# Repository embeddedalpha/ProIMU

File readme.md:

# ProIMU (Under Development)
### A high precision interial measurement unit with altitute and GPS support.

### ProIMU can be operated with and without battery. A 3000 mAh LiPo battery powers the device and can be recharged via USB.

### Features available: 
<li>Yaw  (degrees / rad)</li>
<li>Pitch  (degrees / rad)</li>
<li>Roll   (degrees / rad)</li>
<li>Quaternions (degrees / rad)</li>
<li>Pressure (Pa / Hg)</li>
<li>Altitude </li>
<li>Temperature (C / F) </li>
<li>Longitutde </li>
<li>Lattitude </li>
<li>Raw Accelerometer, Gyroscope & Magnetometer </li>
<li>Direction (N/W/E/S) </li>
</br>

### Communication Protocols Available:

<li>USB</li>
<li>TCP IP Socket</li>
<li>MQTT</li>
</br>

### Project Folders:

    📁 Documentation
    📁 Firmware
    📁 Hardware
        ↳ 📁 3D Model
        ↳ 📁 assembly_outputs
        ↳ 📁 BOM
        ↳ 📁 fab_outputs
        ↳ 📁 position_file
        ↳ 📁 footprints.pretty
        ↳ 📁 kicad_proj
            ↳ 📁 ProIMU_V1
        ↳ 📁 lib_fp.pretty
    📁 Images
    📄 README.md

</br>

### Pinout of the MCU:

</br>

### Communication Protocols used:

<table>
    <tr>
        <th> Protocol
        <th> Instance
        <th> Device
    <!-- </tr>
        <tr>
        <td> UART
        <td> 1
        <td> Debug/Console
    </tr> -->
    <!-- <tr>
        <td> 
        <td> 2
        <td> RS232
    </tr> -->
    <tr>
        <td> 
        <td> 1
        <td> Air602 WiFi Module
    </tr>
    <tr>
        <td> 
        <td> 2
        <td> GNSS Module
    </tr>
    <tr>
        <td> I2C
        <td> 2
        <td> MPU9250
    </tr>
    <tr>
        <td> 
        <td> 2
        <td> BMP280
    <!-- </tr>
        <tr>
        <td> 
        <td> 3
        <td> Fuel Gauge
    </tr> -->
    </tr>
    <!-- <tr>
        <td> SPI
        <td> 1
        <td> MPU9250
    </tr> -->
    <tr>
        <td> SDIO
        <td> 1
        <td> SD Card Module
    </tr>
    <tr>
        <td> USB 
        <td> 1
        <td> USB Port
    </tr>
</table>
</br>

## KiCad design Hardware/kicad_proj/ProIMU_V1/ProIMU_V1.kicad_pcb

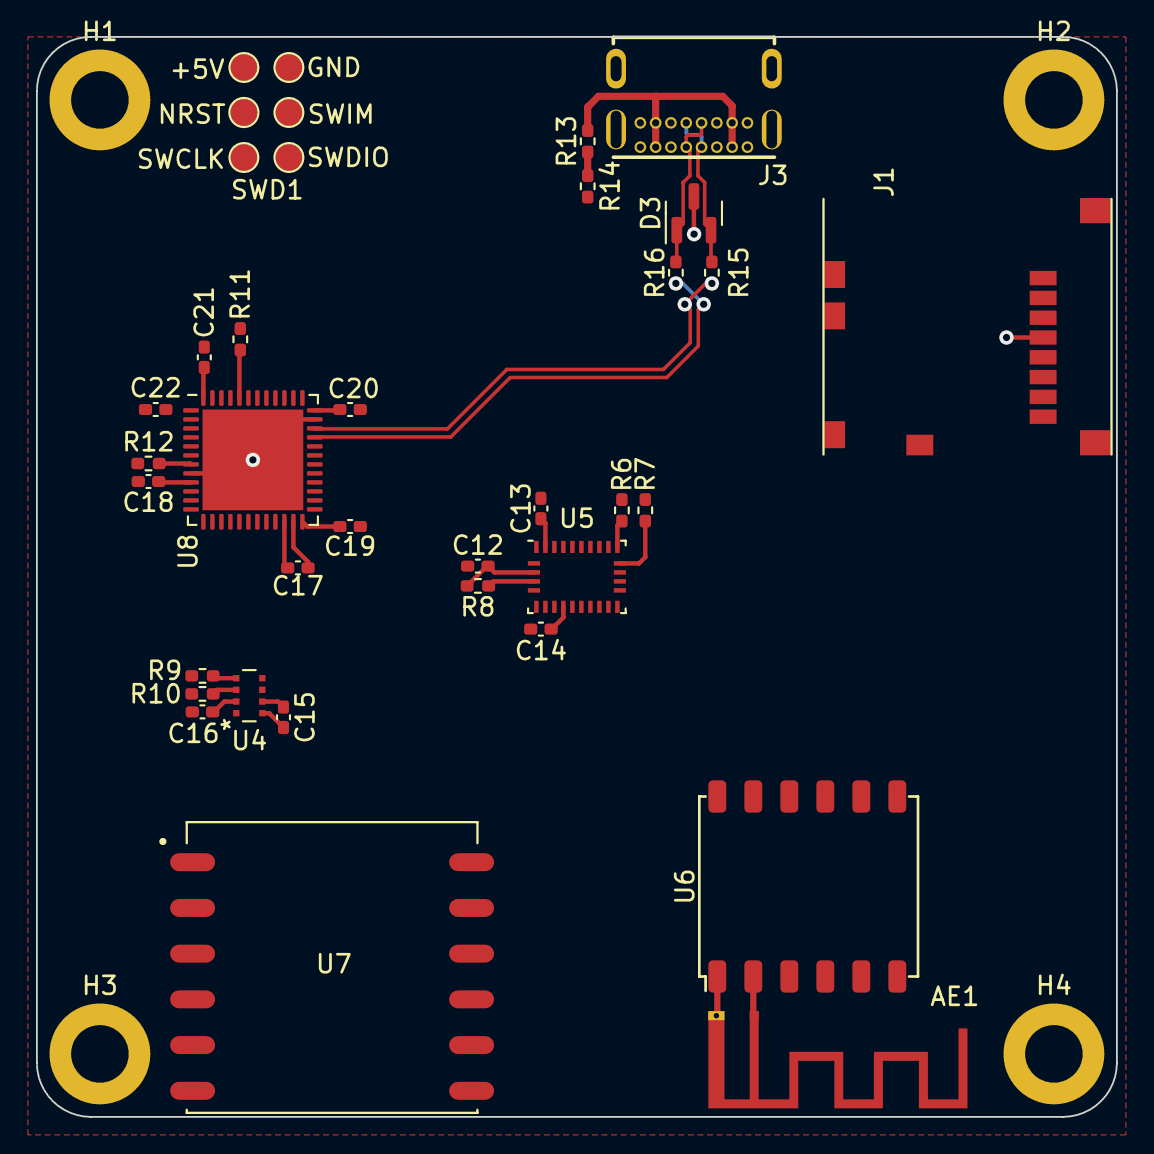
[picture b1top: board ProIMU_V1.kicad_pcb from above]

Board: 4 copper layers, 60.0 x 60.0 mm, 37 parts (1 on the bottom side), 18 nets.

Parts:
AE1: Antenna_Shield; Texas_SWRA117D_2.4GHz_Left
C1, C14, C17, C18, C19, C20, C21, C22: 1uF; C_0402_1005Metric_Pad0.74x0.62mm_HandSolder
C12, C15, C16: 100nF; C_0402_1005Metric_Pad0.74x0.62mm_HandSolder
C13: 120nF; C_0402_1005Metric_Pad0.74x0.62mm_HandSolder
D3: SP0502BAHT; SOT-23
H1, H2, H3, H4: MountingHole; MountingHole_3.2mm_M3_DIN965_Pad
J1: 502570-0893; MOLEX_502570-0893
J3: USB4085-GF-A_REVA4; GCT_USB4085-GF-A_REVA4
R6, R7, R8, R11, R12: 10K; R_0402_1005Metric_Pad0.72x0.64mm_HandSolder
R9, R10: 2.2K; R_0402_1005Metric_Pad0.72x0.64mm_HandSolder
R13, R14: 1K; R_0402_1005Metric_Pad0.72x0.64mm_HandSolder
R15, R16: 22R; R_0402_1005Metric_Pad0.72x0.64mm_HandSolder
SWD1: Conn_02x03_Counter_Clockwise; SWD_POGO_PINS
U4: BMP280
U5: BNO055; LGA-28_5.2x3.8mm_P0.5mm
U6: AIR602
U7: L80-M39; XCVR_L80-M39
U8: STM32F411CEUx; QFN-48-1EP_7x7mm_P0.5mm_EP5.6x5.6mm

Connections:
+3V3: C1.1, C12.2, C13.2, C15.1, C16.1, C18.1, C19.1, C20.1, C21.1, C22.1, J1.4 (VDD), R6.2, R7.2, R8.2, R9.2, R10.2, R11.1, R12.2, U4.2 (CSB), U4.6 (VDDIO), U4.8 (VDD), U5.3 (VDD), U5.6 (PS0), U5.28 (VDDIO), U6.4 (VCC), U7.4 (VCC), U7.5 (V_BCKP), U8.1 (VBAT), U8.9 (VDDA), U8.24 (VDD), U8.36 (VDD), U8.48 (VDD)
/MCU/USB+: R15.2, U8.34 (PA13)
/MCU/USB-: R16.1, U8.33 (PA12)
/Motion_Sensor/BMP280_SCL: R9.1, U4.4 (SCK)
/Motion_Sensor/BMP280_SDA: R10.1, U4.3 (SDI)
/Motion_Sensor/BNO055_SCL: R6.1, U5.20 (COM0)
/Motion_Sensor/BNO055_SDA: R7.1, U5.19 (COM1)
/USB/D+: D3.2 (K), J3.A6 (DP1), J3.B6 (DP2), R15.1
/USB/D-: D3.1 (K), J3.A7 (DN1), J3.B7 (DN2), R16.2
/USB/USB_POWER_IND: R13.1, R14.2
/USB/VBUS: J3.A4 (VBUS), J3.A9 (VBUS), J3.B4 (VBUS), J3.B9 (VBUS), R13.2
GND: AE1.2 (Shield), C1.2, C12.1, C13.1, C14.1, C15.2, C16.2, C17.2, C18.2, C19.2, C20.2, C21.2, C22.2, D3.3 (A), J1.6 (VSS), J3.A1 (GND), J3.A12 (GND), J3.B1 (GND), J3.B12 (GND), R14.1, SWD1.2, U4.1 (GND), U4.5 (SDO), U4.7 (GND), U5.2 (GND), U5.5 (PS1), U5.15 (GNDIO), U5.16 (GNDIO), U5.17 (COM3), U5.18 (COM2), U5.25 (GNDIO), U6.1 (GND), U6.3 (GND), U7.3 (GND), U7.12 (GND), U8.8 (VSSA), U8.23 (VSS), U8.35 (VSS), U8.47 (VSS), U8.49 (VSS)
NRST: R12.1, SWD1.3, U8.7 (NRST)
unnamed: C14.2, U5.9 (CAP)
unnamed: C17.1, U8.22 (VCAP1)
unnamed: R8.1, U5.4 (~BOOT_LOAD_PIN)
unnamed: R11.2, U8.44 (BOOT0)
unnamed: AE1.1 (A), U6.2 (ANT)

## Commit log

2022-02-08 Hardware: First Commit
2022-02-08 Documentation Folder Added with MPU9250 data sheet in it
2022-02-08 BMP280 Datasheet Added
2022-02-08 README.md added
2022-02-08 README.md changed
2022-02-08 Pinout added to Images folder
2022-02-08 README.md updated
2022-02-08 Updated Hardware Files
2022-02-09 09-02-2022 Hardware Update
2022-02-09 Update: Hardware Files. Added Air602 Module
2022-02-09 Update: README.md
2022-02-09 Update: Added Mounting Holes to the schematic
2022-02-09 Add: Documentation:= Air602 Module
2022-02-09 Update: Schematic. Linked 3D models to footprints
2022-02-09 Update: Added Datasheet and Design Maunal Folders
2022-02-10 Udate: Schematic | Added: Footprint allocation for symbols
2022-02-10 Update: PCB Layout
2022-02-10 Update: Layout updated. Pinout needs to be revised
2022-02-11 Update: Layout Sorted. CAN Transreciever to be added and Debug pins to be updated
2022-02-11 Update: Added CAN Transcreceiver
2022-02-13 Update: Added Heirarchial Sheets to simplify the schematic
2022-02-13 Update: Added RS485 TRX Block
2022-02-13 Update: Added USB Isolator and MCU Sheets
2022-02-14 Update: Schematic
2022-02-15 Update: Added Firmware Folder
2022-02-15 Update: Added new files to firmware
2022-02-16 Update: Symbols updated
2022-02-16 Schematic Updated. Removed unecessary schematic pages
2022-02-16 Layout Updated. CAN and RS485 section to be updated
2022-02-16 Added JST 3D model. It's not used
2022-02-16 Added JST Connector
2022-02-16 Added a couple of things. I don't remember now
2022-02-16 Updated Schematic and Layout. Needs more refining
2022-02-17 Added BMP280 Driver
2022-02-17 Added MPU9250 Driver
2022-02-17 Updated Code
2022-02-19 Updated MPU9250.c
2022-02-21 Added new parts
2022-02-21 Updated repo
2022-02-22 Updated Schematic and Layout
2022-02-23 Updated Schematic
2022-02-23 Updated Schematic for battery section
2022-02-23 Updated Schematic and Layout. RS232 and CAN connectors to be interchanged
2022-02-23 Updated Schematic and Layout. Connectors and SD Card Port changed.
2022-02-23 Updated layout
2022-02-23 Updated footprint
2022-02-23 Added BMP280 3D model
2022-02-23 Updated footprints
2022-02-23 Updated Layout. Last commit for the day
2022-02-24 Updated settings and paths
2022-02-24 Updated KiCAD settings
2022-02-25 Updated readme. STM32F412RE replaced by STM32F412CE.
2022-02-25 Updated schematic, layout and footprints
2022-02-26 Updated Layout, schematic, added new symbol and footprint
2022-02-26 Updated symbols
2022-02-26 Updated 3D model
2022-02-26 Updated datasheet
2022-02-27 Removed some footprints
2022-02-27 Updated schematic. Added new isoalted dc/dc converter. Charger circuit needs to be updated
2022-02-28 Removed isolated DC-DC converter and added new regulator in place of it
2022-02-28 Added new schematic for USB and CAN
2022-02-28 Added new schematic for Radio and Isolated UART
2022-02-28 Added sensor schematic
2022-02-28 Updated schematic and removed redundant schematic
2022-02-28 Added rudimentary gerber files. Not be used for any kind of production so please just ignore lol
2022-02-28 removed files
2022-03-02 Added L80 Protocol Specsheet
2022-03-02 added new footprint
2022-03-05 Removed comm protocol as MCU is changed
2022-03-05 Removed features and changed hardware protocol instances is changed
2022-03-07 New Firmware
2022-03-07 Bifurcate the firmware files according to the firmware version
2022-03-12 Updated Files
2022-03-12 Added BNO055 to design and removed MPU9250.
2022-03-12 Added New USB footprint. This will be used through entire project and will not be changed
2022-03-12 Added New USB symbol added.
2022-03-12 Updated layout and schmatics
2022-03-27 Updated Documentation Folder
2022-03-27 Added swd pogo pins footprint
2022-03-27 Updated usb symbol
2022-03-27 Added company logo
2022-03-27 Updated schematic n layput
2022-04-17 Added New 3D Models
2022-04-17 Added New footprints
2022-04-17 Added New Symbols
2022-04-17 Added a completed GPS V1 Schematic
2022-04-17 Added GPS, LoRa and Wifi v1 schematic blocks

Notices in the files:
parts and their libraries:
Copyright 2021 Accelerated Designs. All rights reserved.
